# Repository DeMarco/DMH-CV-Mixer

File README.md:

# DMH-CV-Mixer
5cm Kosmo mixer module focused on CV signals

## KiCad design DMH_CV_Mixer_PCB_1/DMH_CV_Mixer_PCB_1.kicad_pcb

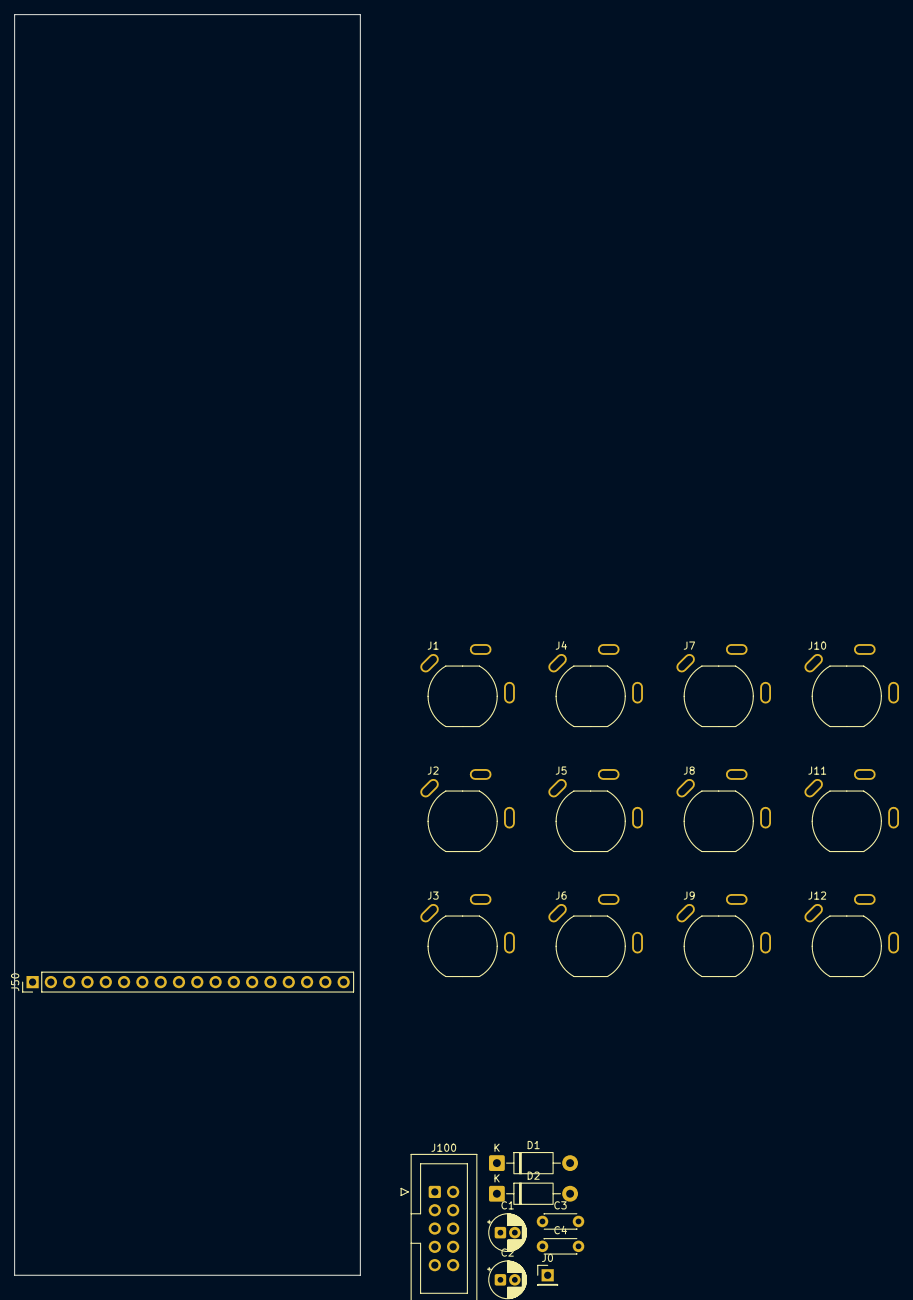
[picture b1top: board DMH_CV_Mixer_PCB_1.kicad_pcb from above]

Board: 2 copper layers, 48.0 x 175.0 mm, 21 parts (0 on the bottom side), 21 nets, no tracks yet.

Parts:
C1, C2: 47uF; CP_Radial_D5.0mm_P2.00mm
C3, C4: 100nF; C_Disc_D4.3mm_W1.9mm_P5.00mm
D1: SB140+; D_DO-41_SOD81_P10.16mm_Horizontal
D2: SB140-; D_DO-41_SOD81_P10.16mm_Horizontal
J0: Conn_01x01; PinHeader_1x01_P2.54mm_Vertical
J1, J2, J3, J4, J5, J6, J7, J8, J9, J10, J11, J12: TS_Jack_6.35mm_Sw; CUI_MJ-63052A
J50: Conn_01x18; PinHeader_1x18_P2.54mm_Vertical
J100: IDC_02x05; IDC-Header_2x05_P2.54mm_Vertical_Eurorack

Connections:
+12V: C1.1, C3.1, D1.1 (K)
-12V: C2.2, C4.2, D2.2 (A)
GND: C1.2, C2.1, C3.2, C4.1, J0.1, J1.S, J2.S, J3.S, J4.S, J5.S, J6.S, J7.S, J8.S, J9.S, J10.S, J11.S, J12.S, J50.1, J50.18, J100.2a, J100.2b, J100.3a, J100.3b, J100.4a, J100.4b
unnamed: D1.2 (A), J100.5a, J100.5b
unnamed: D2.1 (K), J100.1a, J100.1b
unnamed: J1.T, J50.2
unnamed: J2.T, J50.3
unnamed: J3.T, J50.4
unnamed: J3.TN, J50.5
unnamed: J4.T, J50.6
unnamed: J5.T, J50.7
unnamed: J6.T, J50.8
unnamed: J6.TN, J50.9
unnamed: J7.T, J50.10
unnamed: J8.T, J50.11
unnamed: J9.T, J50.12
unnamed: J9.TN, J50.13
unnamed: J10.T, J50.14
unnamed: J11.T, J50.15
unnamed: J12.T, J50.16
unnamed: J12.TN, J50.17

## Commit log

2025-10-07 Created panel project based on VCA bank
2025-10-07 Panel design done
2025-10-08 Created PCB 1 project
2025-10-08 Started IO part design
2025-10-09 Finished IO page
2025-10-09 Schematic in progress
